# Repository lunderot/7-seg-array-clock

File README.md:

# 7 segment array clock
A clock made of 144 individual 7-segment displays. Uses a ESP8266 and MAX7219.

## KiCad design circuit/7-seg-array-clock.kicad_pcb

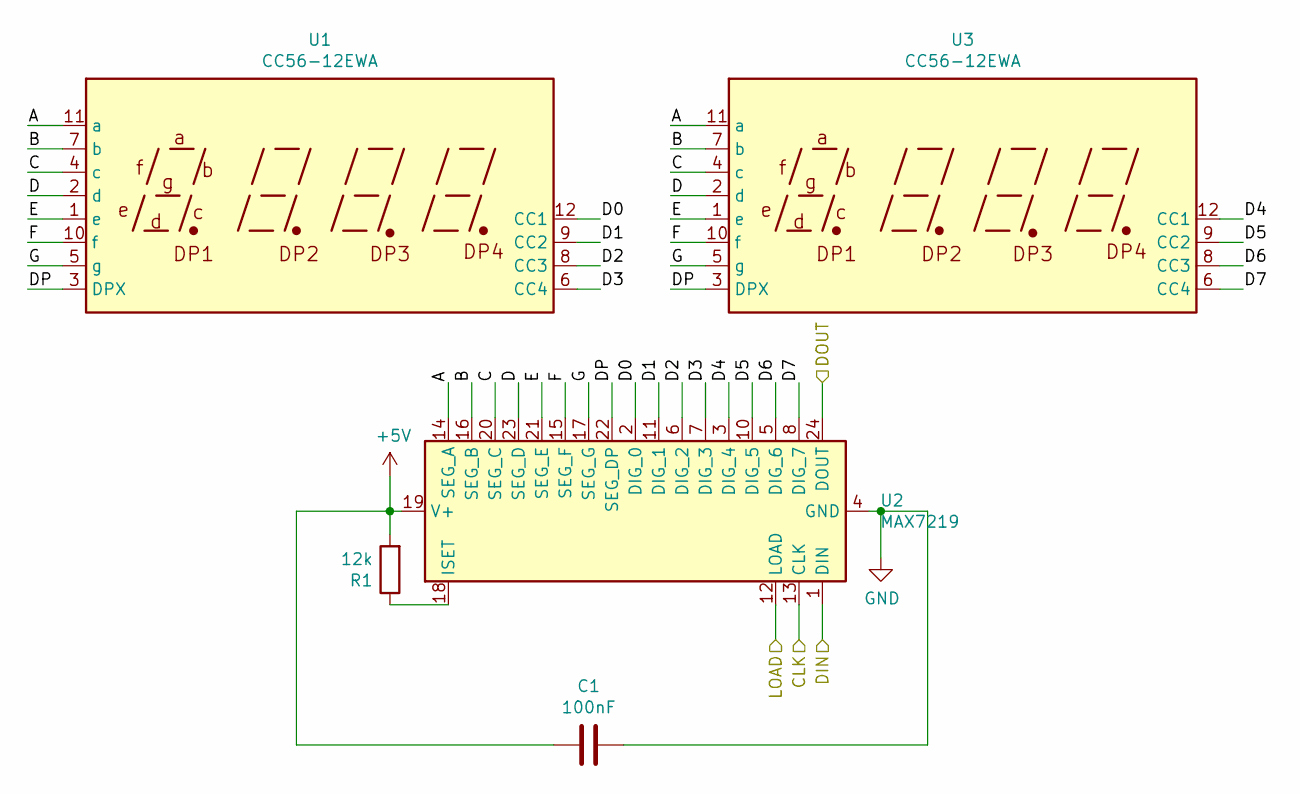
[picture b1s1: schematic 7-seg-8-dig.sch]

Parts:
C1: 100nF; C_0805_2012Metric_Pad1.15x1.40mm_HandSolder
R1: 12k; R_0805_2012Metric_Pad1.15x1.40mm_HandSolder
U1, U3: CC56-12EWA; 7seg
U2: MAX7219; SOIC-24W_7.5x15.4mm_P1.27mm

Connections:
+5V: C1.2, R1.2, U2.19 (V+); also elsewhere on the board
/display0/A: U1.11 (a), U2.14 (SEG_A), U3.11 (a)
/display0/B: U1.7 (b), U2.16 (SEG_B), U3.7 (b)
/display0/C: U1.4 (c), U2.20 (SEG_C), U3.4 (c)
/display0/D: U1.2 (d), U2.23 (SEG_D), U3.2 (d)
/display0/D0: U1.12 (CC1), U2.2 (DIG_0)
/display0/D1: U1.9 (CC2), U2.11 (DIG_1)
/display0/D2: U1.8 (CC3), U2.6 (DIG_2)
/display0/D3: U1.6 (CC4), U2.7 (DIG_3)
/display0/D4: U2.3 (DIG_4), U3.12 (CC1)
/display0/D5: U2.10 (DIG_5), U3.9 (CC2)
/display0/D6: U2.5 (DIG_6), U3.8 (CC3)
/display0/D7: U2.8 (DIG_7), U3.6 (CC4)
/display0/DIN: U2.1 (DIN); also elsewhere on the board
/display0/DP: U1.3 (DPX), U2.22 (SEG_DP), U3.3 (DPX)
/display0/E: U1.1 (e), U2.21 (SEG_E), U3.1 (e)
/display0/F: U1.10 (f), U2.15 (SEG_F), U3.10 (f)
/display0/G: U1.5 (g), U2.17 (SEG_G), U3.5 (g)
/display1/DIN: U2.24 (DOUT); also elsewhere on the board
CLK: U2.13 (CLK); also elsewhere on the board
GND: C1.1, U2.4 (GND), U2.9 (GND); also elsewhere on the board
LOAD: U2.12 (LOAD); also elsewhere on the board
unnamed: R1.1, U2.18 (ISET)

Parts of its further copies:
C2, C3, C4, C5, C6, C7, C8, C9, C10, C11, C12, C13, C14, C15, C16, C17, C18: 100nF; C_0805_2012Metric_Pad1.15x1.40mm_HandSolder
R2, R3, R4, R5, R6, R7, R8, R9, R10, R11, R12, R13, R14, R15, R16, R17, R18: 12k; R_0805_2012Metric_Pad1.15x1.40mm_HandSolder
U4, U6, U8, U10, U11, U13, U14, U16, U17, U19, U20, U22, U23, U25, U26, U28, U29, U31, U32, U34, U35, U37, U38, U40, U41, U43, U44, U46, U47, U49, U50, U52, U53, U55: CC56-12EWA; 7seg
U5, U9, U12, U15, U18, U21, U24, U27, U30, U33, U36, U39, U42, U45, U48, U51, U54: MAX7219; SOIC-24W_7.5x15.4mm_P1.27mm

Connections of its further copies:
+5V: C2.2, C3.2, C4.2, C5.2, C6.2, C7.2, C8.2, C9.2, C10.2, C11.2, C12.2, C13.2, C14.2, C15.2, C16.2, C17.2, C18.2, R2.2, R3.2, R4.2, R5.2, R6.2, R7.2, R8.2, R9.2, R10.2, R11.2, R12.2, R13.2, R14.2, R15.2, R16.2, R17.2, R18.2, U5.19 (V+), U9.19 (V+), U12.19 (V+), U15.19 (V+), U18.19 (V+), U21.19 (V+), U24.19 (V+), U27.19 (V+), U30.19 (V+), U33.19 (V+), U36.19 (V+), U39.19 (V+), U42.19 (V+), U45.19 (V+), U48.19 (V+), U51.19 (V+), U54.19 (V+); also elsewhere on the board
/display1/A: U4.11 (a), U5.14 (SEG_A), U6.11 (a)
/display1/B: U4.7 (b), U5.16 (SEG_B), U6.7 (b)
/display1/C: U4.4 (c), U5.20 (SEG_C), U6.4 (c)
/display1/D: U4.2 (d), U5.23 (SEG_D), U6.2 (d)
/display1/D0: U4.12 (CC1), U5.2 (DIG_0)
/display1/D1: U4.9 (CC2), U5.11 (DIG_1)
/display1/D2: U4.8 (CC3), U5.6 (DIG_2)
/display1/D3: U4.6 (CC4), U5.7 (DIG_3)
/display1/D4: U5.3 (DIG_4), U6.12 (CC1)
/display1/D5: U5.10 (DIG_5), U6.9 (CC2)
/display1/D6: U5.5 (DIG_6), U6.8 (CC3)
/display1/D7: U5.8 (DIG_7), U6.6 (CC4)
/display1/DIN: U5.1 (DIN); also elsewhere on the board
/display1/DP: U4.3 (DPX), U5.22 (SEG_DP), U6.3 (DPX)
/display1/E: U4.1 (e), U5.21 (SEG_E), U6.1 (e)
/display1/F: U4.10 (f), U5.15 (SEG_F), U6.10 (f)
/display1/G: U4.5 (g), U5.17 (SEG_G), U6.5 (g)
/display3/A: U8.11 (a), U9.14 (SEG_A), U10.11 (a)
/display3/B: U8.7 (b), U9.16 (SEG_B), U10.7 (b)
/display3/C: U8.4 (c), U9.20 (SEG_C), U10.4 (c)
/display3/D: U8.2 (d), U9.23 (SEG_D), U10.2 (d)
/display3/D0: U8.12 (CC1), U9.2 (DIG_0)
/display3/D1: U8.9 (CC2), U9.11 (DIG_1)
/display3/D2: U8.8 (CC3), U9.6 (DIG_2)
/display3/D3: U8.6 (CC4), U9.7 (DIG_3)
/display3/D4: U9.3 (DIG_4), U10.12 (CC1)
/display3/D5: U9.10 (DIG_5), U10.9 (CC2)
/display3/D6: U9.5 (DIG_6), U10.8 (CC3)
/display3/D7: U9.8 (DIG_7), U10.6 (CC4)
/display3/DIN: U5.24 (DOUT), U9.1 (DIN)
/display3/DP: U8.3 (DPX), U9.22 (SEG_DP), U10.3 (DPX)
/display3/E: U8.1 (e), U9.21 (SEG_E), U10.1 (e)
/display3/F: U8.10 (f), U9.15 (SEG_F), U10.10 (f)
/display3/G: U8.5 (g), U9.17 (SEG_G), U10.5 (g)
/display4/A: U11.11 (a), U12.14 (SEG_A), U13.11 (a)
/display4/B: U11.7 (b), U12.16 (SEG_B), U13.7 (b)
/display4/C: U11.4 (c), U12.20 (SEG_C), U13.4 (c)
/display4/D: U11.2 (d), U12.23 (SEG_D), U13.2 (d)
/display4/D0: U11.12 (CC1), U12.2 (DIG_0)
/display4/D1: U11.9 (CC2), U12.11 (DIG_1)
/display4/D2: U11.8 (CC3), U12.6 (DIG_2)
/display4/D3: U11.6 (CC4), U12.7 (DIG_3)
/display4/D4: U12.3 (DIG_4), U13.12 (CC1)
/display4/D5: U12.10 (DIG_5), U13.9 (CC2)
/display4/D6: U12.5 (DIG_6), U13.8 (CC3)
/display4/D7: U12.8 (DIG_7), U13.6 (CC4)
/display4/DIN: U9.24 (DOUT), U12.1 (DIN)
/display4/DP: U11.3 (DPX), U12.22 (SEG_DP), U13.3 (DPX)
/display4/E: U11.1 (e), U12.21 (SEG_E), U13.1 (e)
/display4/F: U11.10 (f), U12.15 (SEG_F), U13.10 (f)
/display4/G: U11.5 (g), U12.17 (SEG_G), U13.5 (g)
/display5/A: U14.11 (a), U15.14 (SEG_A), U16.11 (a)
/display5/B: U14.7 (b), U15.16 (SEG_B), U16.7 (b)
/display5/C: U14.4 (c), U15.20 (SEG_C), U16.4 (c)
/display5/D: U14.2 (d), U15.23 (SEG_D), U16.2 (d)
/display5/D0: U14.12 (CC1), U15.2 (DIG_0)
/display5/D1: U14.9 (CC2), U15.11 (DIG_1)
/display5/D2: U14.8 (CC3), U15.6 (DIG_2)
/display5/D3: U14.6 (CC4), U15.7 (DIG_3)
/display5/D4: U15.3 (DIG_4), U16.12 (CC1)
/display5/D5: U15.10 (DIG_5), U16.9 (CC2)
/display5/D6: U15.5 (DIG_6), U16.8 (CC3)
/display5/D7: U15.8 (DIG_7), U16.6 (CC4)
/display5/DIN: U12.24 (DOUT), U15.1 (DIN)
/display5/DP: U14.3 (DPX), U15.22 (SEG_DP), U16.3 (DPX)
/display5/E: U14.1 (e), U15.21 (SEG_E), U16.1 (e)
/display5/F: U14.10 (f), U15.15 (SEG_F), U16.10 (f)
/display5/G: U14.5 (g), U15.17 (SEG_G), U16.5 (g)
/display6/A: U17.11 (a), U18.14 (SEG_A), U19.11 (a)
/display6/B: U17.7 (b), U18.16 (SEG_B), U19.7 (b)
/display6/C: U17.4 (c), U18.20 (SEG_C), U19.4 (c)
/display6/D: U17.2 (d), U18.23 (SEG_D), U19.2 (d)
/display6/D0: U17.12 (CC1), U18.2 (DIG_0)
/display6/D1: U17.9 (CC2), U18.11 (DIG_1)
/display6/D2: U17.8 (CC3), U18.6 (DIG_2)
/display6/D3: U17.6 (CC4), U18.7 (DIG_3)
/display6/D4: U18.3 (DIG_4), U19.12 (CC1)
/display6/D5: U18.10 (DIG_5), U19.9 (CC2)
/display6/D6: U18.5 (DIG_6), U19.8 (CC3)
/display6/D7: U18.8 (DIG_7), U19.6 (CC4)
/display6/DIN: U15.24 (DOUT), U18.1 (DIN)
/display6/DP: U17.3 (DPX), U18.22 (SEG_DP), U19.3 (DPX)
/display6/E: U17.1 (e), U18.21 (SEG_E), U19.1 (e)
/display6/F: U17.10 (f), U18.15 (SEG_F), U19.10 (f)
/display6/G: U17.5 (g), U18.17 (SEG_G), U19.5 (g)
/display7/A: U20.11 (a), U21.14 (SEG_A), U22.11 (a)
/display7/B: U20.7 (b), U21.16 (SEG_B), U22.7 (b)
/display7/C: U20.4 (c), U21.20 (SEG_C), U22.4 (c)
/display7/D: U20.2 (d), U21.23 (SEG_D), U22.2 (d)
/display7/D0: U20.12 (CC1), U21.2 (DIG_0)
/display7/D1: U20.9 (CC2), U21.11 (DIG_1)
/display7/D2: U20.8 (CC3), U21.6 (DIG_2)
/display7/D3: U20.6 (CC4), U21.7 (DIG_3)
/display7/D4: U21.3 (DIG_4), U22.12 (CC1)
/display7/D5: U21.10 (DIG_5), U22.9 (CC2)
/display7/D6: U21.5 (DIG_6), U22.8 (CC3)
/display7/D7: U21.8 (DIG_7), U22.6 (CC4)
/display7/DIN: U18.24 (DOUT), U21.1 (DIN)
/display7/DP: U20.3 (DPX), U21.22 (SEG_DP), U22.3 (DPX)
/display7/E: U20.1 (e), U21.21 (SEG_E), U22.1 (e)
/display7/F: U20.10 (f), U21.15 (SEG_F), U22.10 (f)
/display7/G: U20.5 (g), U21.17 (SEG_G), U22.5 (g)
/display8/A: U23.11 (a), U24.14 (SEG_A), U25.11 (a)
/display8/B: U23.7 (b), U24.16 (SEG_B), U25.7 (b)
/display8/C: U23.4 (c), U24.20 (SEG_C), U25.4 (c)
/display8/D: U23.2 (d), U24.23 (SEG_D), U25.2 (d)
/display8/D0: U23.12 (CC1), U24.2 (DIG_0)
/display8/D1: U23.9 (CC2), U24.11 (DIG_1)
/display8/D2: U23.8 (CC3), U24.6 (DIG_2)
/display8/D3: U23.6 (CC4), U24.7 (DIG_3)
/display8/D4: U24.3 (DIG_4), U25.12 (CC1)
/display8/D5: U24.10 (DIG_5), U25.9 (CC2)
/display8/D6: U24.5 (DIG_6), U25.8 (CC3)
/display8/D7: U24.8 (DIG_7), U25.6 (CC4)
/display8/DIN: U21.24 (DOUT), U24.1 (DIN)
/display8/DP: U23.3 (DPX), U24.22 (SEG_DP), U25.3 (DPX)
/display8/E: U23.1 (e), U24.21 (SEG_E), U25.1 (e)
/display8/F: U23.10 (f), U24.15 (SEG_F), U25.10 (f)
/display8/G: U23.5 (g), U24.17 (SEG_G), U25.5 (g)
/display9/A: U26.11 (a), U27.14 (SEG_A), U28.11 (a)
/display9/B: U26.7 (b), U27.16 (SEG_B), U28.7 (b)
/display9/C: U26.4 (c), U27.20 (SEG_C), U28.4 (c)
/display9/D: U26.2 (d), U27.23 (SEG_D), U28.2 (d)
/display9/D0: U26.12 (CC1), U27.2 (DIG_0)
/display9/D1: U26.9 (CC2), U27.11 (DIG_1)
/display9/D2: U26.8 (CC3), U27.6 (DIG_2)
/display9/D3: U26.6 (CC4), U27.7 (DIG_3)
/display9/D4: U27.3 (DIG_4), U28.12 (CC1)
/display9/D5: U27.10 (DIG_5), U28.9 (CC2)
/display9/D6: U27.5 (DIG_6), U28.8 (CC3)
/display9/D7: U27.8 (DIG_7), U28.6 (CC4)
/display9/DIN: U24.24 (DOUT), U27.1 (DIN)
/display9/DP: U26.3 (DPX), U27.22 (SEG_DP), U28.3 (DPX)
/display9/E: U26.1 (e), U27.21 (SEG_E), U28.1 (e)
/display9/F: U26.10 (f), U27.15 (SEG_F), U28.10 (f)
/display9/G: U26.5 (g), U27.17 (SEG_G), U28.5 (g)
/display10/A: U29.11 (a), U30.14 (SEG_A), U31.11 (a)
/display10/B: U29.7 (b), U30.16 (SEG_B), U31.7 (b)
/display10/C: U29.4 (c), U30.20 (SEG_C), U31.4 (c)
/display10/D: U29.2 (d), U30.23 (SEG_D), U31.2 (d)
/display10/D0: U29.12 (CC1), U30.2 (DIG_0)
/display10/D1: U29.9 (CC2), U30.11 (DIG_1)
/display10/D2: U29.8 (CC3), U30.6 (DIG_2)
/display10/D3: U29.6 (CC4), U30.7 (DIG_3)
/display10/D4: U30.3 (DIG_4), U31.12 (CC1)
/display10/D5: U30.10 (DIG_5), U31.9 (CC2)
/display10/D6: U30.5 (DIG_6), U31.8 (CC3)
/display10/D7: U30.8 (DIG_7), U31.6 (CC4)
/display10/DIN: U27.24 (DOUT), U30.1 (DIN)
/display10/DP: U29.3 (DPX), U30.22 (SEG_DP), U31.3 (DPX)
/display10/E: U29.1 (e), U30.21 (SEG_E), U31.1 (e)
/display10/F: U29.10 (f), U30.15 (SEG_F), U31.10 (f)
/display10/G: U29.5 (g), U30.17 (SEG_G), U31.5 (g)
/display11/A: U32.11 (a), U33.14 (SEG_A), U34.11 (a)
/display11/B: U32.7 (b), U33.16 (SEG_B), U34.7 (b)
/display11/C: U32.4 (c), U33.20 (SEG_C), U34.4 (c)
/display11/D: U32.2 (d), U33.23 (SEG_D), U34.2 (d)
/display11/D0: U32.12 (CC1), U33.2 (DIG_0)
/display11/D1: U32.9 (CC2), U33.11 (DIG_1)
/display11/D2: U32.8 (CC3), U33.6 (DIG_2)
/display11/D3: U32.6 (CC4), U33.7 (DIG_3)
/display11/D4: U33.3 (DIG_4), U34.12 (CC1)
/display11/D5: U33.10 (DIG_5), U34.9 (CC2)
/display11/D6: U33.5 (DIG_6), U34.8 (CC3)
/display11/D7: U33.8 (DIG_7), U34.6 (CC4)
/display11/DIN: U30.24 (DOUT), U33.1 (DIN)
/display11/DP: U32.3 (DPX), U33.22 (SEG_DP), U34.3 (DPX)
/display11/E: U32.1 (e), U33.21 (SEG_E), U34.1 (e)
/display11/F: U32.10 (f), U33.15 (SEG_F), U34.10 (f)
/display11/G: U32.5 (g), U33.17 (SEG_G), U34.5 (g)
/display12/A: U35.11 (a), U36.14 (SEG_A), U37.11 (a)
/display12/B: U35.7 (b), U36.16 (SEG_B), U37.7 (b)
/display12/C: U35.4 (c), U36.20 (SEG_C), U37.4 (c)
/display12/D: U35.2 (d), U36.23 (SEG_D), U37.2 (d)
/display12/D0: U35.12 (CC1), U36.2 (DIG_0)
/display12/D1: U35.9 (CC2), U36.11 (DIG_1)
/display12/D2: U35.8 (CC3), U36.6 (DIG_2)
/display12/D3: U35.6 (CC4), U36.7 (DIG_3)
/display12/D4: U36.3 (DIG_4), U37.12 (CC1)
/display12/D5: U36.10 (DIG_5), U37.9 (CC2)
/display12/D6: U36.5 (DIG_6), U37.8 (CC3)
/display12/D7: U36.8 (DIG_7), U37.6 (CC4)
/display12/DIN: U33.24 (DOUT), U36.1 (DIN)
/display12/DP: U35.3 (DPX), U36.22 (SEG_DP), U37.3 (DPX)
/display12/E: U35.1 (e), U36.21 (SEG_E), U37.1 (e)
/display12/F: U35.10 (f), U36.15 (SEG_F), U37.10 (f)
/display12/G: U35.5 (g), U36.17 (SEG_G), U37.5 (g)
/display13/A: U38.11 (a), U39.14 (SEG_A), U40.11 (a)
/display13/B: U38.7 (b), U39.16 (SEG_B), U40.7 (b)
/display13/C: U38.4 (c), U39.20 (SEG_C), U40.4 (c)
/display13/D: U38.2 (d), U39.23 (SEG_D), U40.2 (d)
/display13/D0: U38.12 (CC1), U39.2 (DIG_0)
/display13/D1: U38.9 (CC2), U39.11 (DIG_1)
/display13/D2: U38.8 (CC3), U39.6 (DIG_2)
/display13/D3: U38.6 (CC4), U39.7 (DIG_3)
/display13/D4: U39.3 (DIG_4), U40.12 (CC1)
/display13/D5: U39.10 (DIG_5), U40.9 (CC2)
/display13/D6: U39.5 (DIG_6), U40.8 (CC3)
/display13/D7: U39.8 (DIG_7), U40.6 (CC4)
/display13/DIN: U36.24 (DOUT), U39.1 (DIN)
/display13/DP: U38.3 (DPX), U39.22 (SEG_DP), U40.3 (DPX)
/display13/E: U38.1 (e), U39.21 (SEG_E), U40.1 (e)
/display13/F: U38.10 (f), U39.15 (SEG_F), U40.10 (f)
/display13/G: U38.5 (g), U39.17 (SEG_G), U40.5 (g)
/display14/A: U41.11 (a), U42.14 (SEG_A), U43.11 (a)
/display14/B: U41.7 (b), U42.16 (SEG_B), U43.7 (b)
/display14/C: U41.4 (c), U42.20 (SEG_C), U43.4 (c)
/display14/D: U41.2 (d), U42.23 (SEG_D), U43.2 (d)
/display14/D0: U41.12 (CC1), U42.2 (DIG_0)
/display14/D1: U41.9 (CC2), U42.11 (DIG_1)
/display14/D2: U41.8 (CC3), U42.6 (DIG_2)
/display14/D3: U41.6 (CC4), U42.7 (DIG_3)
/display14/D4: U42.3 (DIG_4), U43.12 (CC1)
/display14/D5: U42.10 (DIG_5), U43.9 (CC2)
/display14/D6: U42.5 (DIG_6), U43.8 (CC3)
/display14/D7: U42.8 (DIG_7), U43.6 (CC4)
/display14/DIN: U39.24 (DOUT), U42.1 (DIN)
/display14/DP: U41.3 (DPX), U42.22 (SEG_DP), U43.3 (DPX)
/display14/E: U41.1 (e), U42.21 (SEG_E), U43.1 (e)
/display14/F: U41.10 (f), U42.15 (SEG_F), U43.10 (f)
/display14/G: U41.5 (g), U42.17 (SEG_G), U43.5 (g)
/display15/A: U44.11 (a), U45.14 (SEG_A), U46.11 (a)
/display15/B: U44.7 (b), U45.16 (SEG_B), U46.7 (b)
/display15/C: U44.4 (c), U45.20 (SEG_C), U46.4 (c)
/display15/D: U44.2 (d), U45.23 (SEG_D), U46.2 (d)
/display15/D0: U44.12 (CC1), U45.2 (DIG_0)
/display15/D1: U44.9 (CC2), U45.11 (DIG_1)
/display15/D2: U44.8 (CC3), U45.6 (DIG_2)
/display15/D3: U44.6 (CC4), U45.7 (DIG_3)
/display15/D4: U45.3 (DIG_4), U46.12 (CC1)
/display15/D5: U45.10 (DIG_5), U46.9 (CC2)
/display15/D6: U45.5 (DIG_6), U46.8 (CC3)
/display15/D7: U45.8 (DIG_7), U46.6 (CC4)
/display15/DIN: U42.24 (DOUT), U45.1 (DIN)
/display15/DP: U44.3 (DPX), U45.22 (SEG_DP), U46.3 (DPX)
/display15/E: U44.1 (e), U45.21 (SEG_E), U46.1 (e)
/display15/F: U44.10 (f), U45.15 (SEG_F), U46.10 (f)
/display15/G: U44.5 (g), U45.17 (SEG_G), U46.5 (g)
/display16/A: U47.11 (a), U48.14 (SEG_A), U49.11 (a)
/display16/B: U47.7 (b), U48.16 (SEG_B), U49.7 (b)
/display16/C: U47.4 (c), U48.20 (SEG_C), U49.4 (c)
/display16/D: U47.2 (d), U48.23 (SEG_D), U49.2 (d)
/display16/D0: U47.12 (CC1), U48.2 (DIG_0)
/display16/D1: U47.9 (CC2), U48.11 (DIG_1)
/display16/D2: U47.8 (CC3), U48.6 (DIG_2)
/display16/D3: U47.6 (CC4), U48.7 (DIG_3)
/display16/D4: U48.3 (DIG_4), U49.12 (CC1)
/display16/D5: U48.10 (DIG_5), U49.9 (CC2)
/display16/D6: U48.5 (DIG_6), U49.8 (CC3)
/display16/D7: U48.8 (DIG_7), U49.6 (CC4)
/display16/DIN: U45.24 (DOUT), U48.1 (DIN)
/display16/DP: U47.3 (DPX), U48.22 (SEG_DP), U49.3 (DPX)
/display16/E: U47.1 (e), U48.21 (SEG_E), U49.1 (e)
/display16/F: U47.10 (f), U48.15 (SEG_F), U49.10 (f)
/display16/G: U47.5 (g), U48.17 (SEG_G), U49.5 (g)
/display17/A: U50.11 (a), U51.14 (SEG_A), U52.11 (a)
/display17/B: U50.7 (b), U51.16 (SEG_B), U52.7 (b)
/display17/C: U50.4 (c), U51.20 (SEG_C), U52.4 (c)
/display17/D: U50.2 (d), U51.23 (SEG_D), U52.2 (d)
/display17/D0: U50.12 (CC1), U51.2 (DIG_0)
/display17/D1: U50.9 (CC2), U51.11 (DIG_1)
/display17/D2: U50.8 (CC3), U51.6 (DIG_2)
/display17/D3: U50.6 (CC4), U51.7 (DIG_3)
/display17/D4: U51.3 (DIG_4), U52.12 (CC1)
/display17/D5: U51.10 (DIG_5), U52.9 (CC2)
/display17/D6: U51.5 (DIG_6), U52.8 (CC3)
/display17/D7: U51.8 (DIG_7), U52.6 (CC4)
/display17/DIN: U48.24 (DOUT), U51.1 (DIN)
/display17/DP: U50.3 (DPX), U51.22 (SEG_DP), U52.3 (DPX)
/display17/E: U50.1 (e), U51.21 (SEG_E), U52.1 (e)
/display17/F: U50.10 (f), U51.15 (SEG_F), U52.10 (f)
/display17/G: U50.5 (g), U51.17 (SEG_G), U52.5 (g)
/display18/A: U53.11 (a), U54.14 (SEG_A), U55.11 (a)
/display18/B: U53.7 (b), U54.16 (SEG_B), U55.7 (b)
/display18/C: U53.4 (c), U54.20 (SEG_C), U55.4 (c)
/display18/D: U53.2 (d), U54.23 (SEG_D), U55.2 (d)
/display18/D0: U53.12 (CC1), U54.2 (DIG_0)
/display18/D1: U53.9 (CC2), U54.11 (DIG_1)
/display18/D2: U53.8 (CC3), U54.6 (DIG_2)
/display18/D3: U53.6 (CC4), U54.7 (DIG_3)
/display18/D4: U54.3 (DIG_4), U55.12 (CC1)
/display18/D5: U54.10 (DIG_5), U55.9 (CC2)
/display18/D6: U54.5 (DIG_6), U55.8 (CC3)
/display18/D7: U54.8 (DIG_7), U55.6 (CC4)
/display18/DIN: U51.24 (DOUT), U54.1 (DIN)
/display18/DOUT: U54.24 (DOUT)
/display18/DP: U53.3 (DPX), U54.22 (SEG_DP), U55.3 (DPX)
/display18/E: U53.1 (e), U54.21 (SEG_E), U55.1 (e)
/display18/F: U53.10 (f), U54.15 (SEG_F), U55.10 (f)
/display18/G: U53.5 (g), U54.17 (SEG_G), U55.5 (g)
CLK: U5.13 (CLK), U9.13 (CLK), U12.13 (CLK), U15.13 (CLK), U18.13 (CLK), U21.13 (CLK), U24.13 (CLK), U27.13 (CLK), U30.13 (CLK), U33.13 (CLK), U36.13 (CLK), U39.13 (CLK), U42.13 (CLK), U45.13 (CLK), U48.13 (CLK), U51.13 (CLK), U54.13 (CLK); also elsewhere on the board
GND: C2.1, C3.1, C4.1, C5.1, C6.1, C7.1, C8.1, C9.1, C10.1, C11.1, C12.1, C13.1, C14.1, C15.1, C16.1, C17.1, C18.1, U5.4 (GND), U5.9 (GND), U9.4 (GND), U9.9 (GND), U12.4 (GND), U12.9 (GND), U15.4 (GND), U15.9 (GND), U18.4 (GND), U18.9 (GND), U21.4 (GND), U21.9 (GND), U24.4 (GND), U24.9 (GND), U27.4 (GND), U27.9 (GND), U30.4 (GND), U30.9 (GND), U33.4 (GND), U33.9 (GND), U36.4 (GND), U36.9 (GND), U39.4 (GND), U39.9 (GND), U42.4 (GND), U42.9 (GND), U45.4 (GND), U45.9 (GND), U48.4 (GND), U48.9 (GND), U51.4 (GND), U51.9 (GND), U54.4 (GND), U54.9 (GND); also elsewhere on the board
LOAD: U5.12 (LOAD), U9.12 (LOAD), U12.12 (LOAD), U15.12 (LOAD), U18.12 (LOAD), U21.12 (LOAD), U24.12 (LOAD), U27.12 (LOAD), U30.12 (LOAD), U33.12 (LOAD), U36.12 (LOAD), U39.12 (LOAD), U42.12 (LOAD), U45.12 (LOAD), U48.12 (LOAD), U51.12 (LOAD), U54.12 (LOAD); also elsewhere on the board
unnamed: R2.1, U5.18 (ISET)
unnamed: R3.1, U9.18 (ISET)
unnamed: R4.1, U12.18 (ISET)
unnamed: R5.1, U15.18 (ISET)
unnamed: R6.1, U18.18 (ISET)
unnamed: R7.1, U21.18 (ISET)
unnamed: R8.1, U24.18 (ISET)
unnamed: R9.1, U27.18 (ISET)
unnamed: R10.1, U30.18 (ISET)
unnamed: R11.1, U33.18 (ISET)
unnamed: R12.1, U36.18 (ISET)
unnamed: R13.1, U39.18 (ISET)
unnamed: R14.1, U42.18 (ISET)
unnamed: R15.1, U45.18 (ISET)
unnamed: R16.1, U48.18 (ISET)
unnamed: R17.1, U51.18 (ISET)
unnamed: R18.1, U54.18 (ISET)

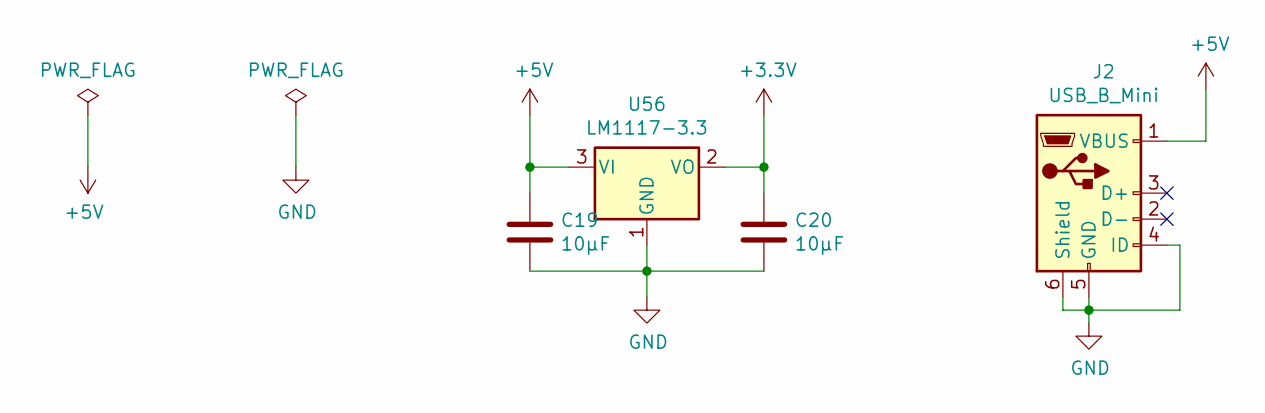
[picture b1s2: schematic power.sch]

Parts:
C19, C20: 10µF; C_0805_2012Metric_Pad1.15x1.40mm_HandSolder
J2: USB_B_Mini; USB_Mini-B_Lumberg_2486_01_Horizontal
U56: LM1117-3.3; SOT-223-3_TabPin2

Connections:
+3V3: C20.1, U56.2 (VO); also elsewhere on the board
+5V: C19.1, J2.1 (VBUS), U56.3 (VI); also elsewhere on the board
GND: C19.2, C20.2, J2.4 (ID), J2.5 (GND), J2.6 (Shield), U56.1 (GND); also elsewhere on the board

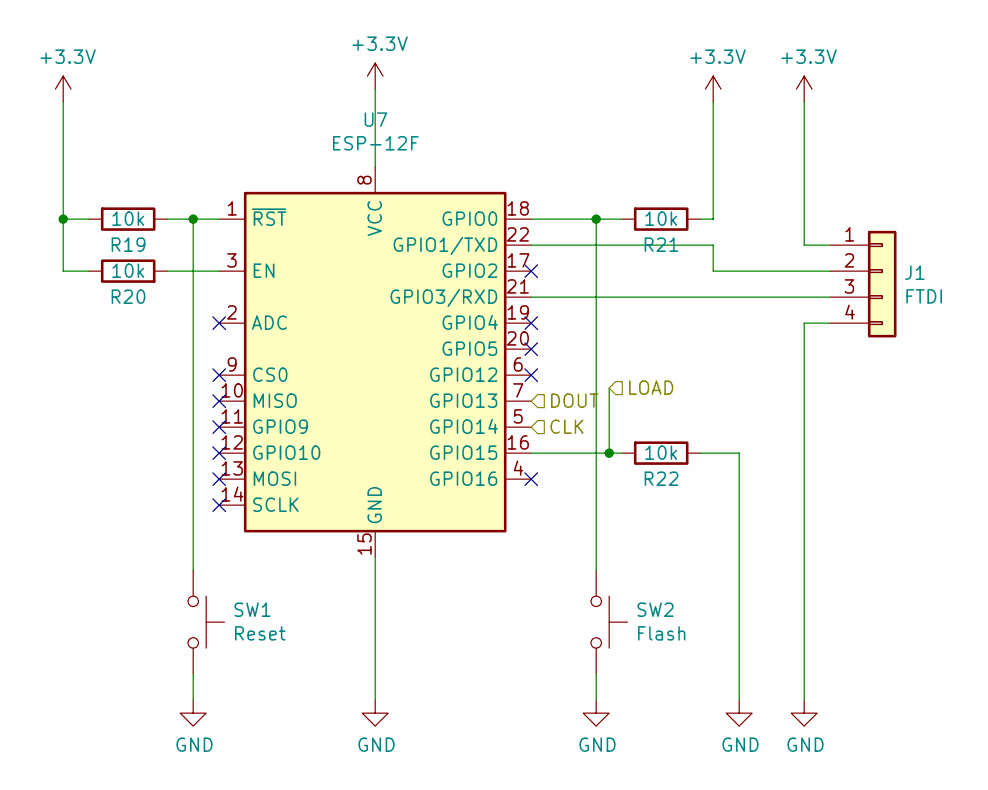
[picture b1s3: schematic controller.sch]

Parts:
J1: FTDI; PinHeader_1x04_P2.54mm_Vertical
R19, R20, R21, R22: 10k; R_0805_2012Metric_Pad1.15x1.40mm_HandSolder
SW1: Reset; SW_SPST_CK_RS282G05A3
SW2: Flash; SW_SPST_CK_RS282G05A3
U7: ESP-12F; ESP-12E

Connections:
+3V3: J1.1, R19.2, R20.1, R21.1, U7.8 (VCC); also elsewhere on the board
/display0/DIN: U7.7 (GPIO13); also elsewhere on the board
CLK: U7.5 (GPIO14); also elsewhere on the board
GND: J1.4, R22.1, SW1.2, SW2.2, U7.15 (GND); also elsewhere on the board
LOAD: R22.2, U7.16 (GPIO15); also elsewhere on the board
unnamed: J1.2, U7.22 (GPIO1/TXD)
unnamed: J1.3, U7.21 (GPIO3/RXD)
unnamed: R19.1, SW1.1, U7.1 (~RST)
unnamed: R20.2, U7.3 (EN)
unnamed: R21.2, SW2.1, U7.18 (GPIO0)

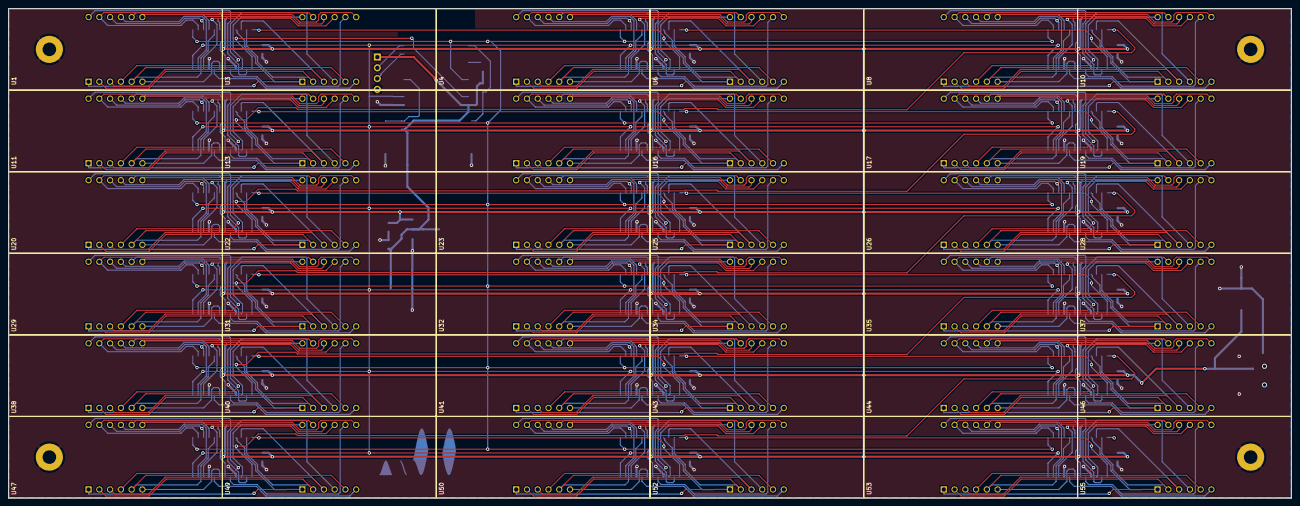
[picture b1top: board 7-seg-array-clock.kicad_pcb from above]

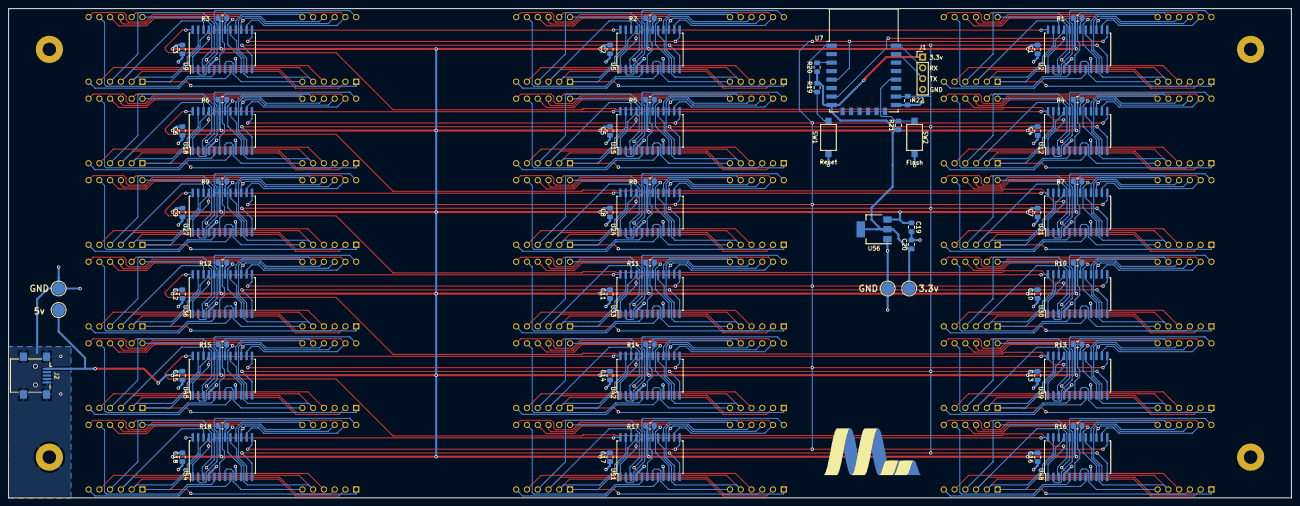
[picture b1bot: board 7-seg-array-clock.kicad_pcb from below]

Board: 2 copper layers, 302.6 x 115.4 mm, 102 parts (66 on the bottom side), 334 nets.

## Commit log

2020-02-01 Completed display circuit and made basic PCB layout
2020-02-01 Added tracks to first display
2020-02-02 Routed all displays
2020-02-02 Updated display footprint
2020-02-02 Added PCB screenshots
2020-02-02 Fixed display clearance issues
2020-02-02 Updated footprint to the proper one
2020-02-05 Added microcontroller circuit
2020-02-09 Added controller to PCB
2020-02-09 Finished PCB
2020-02-23 Added mouting holes
2020-02-23 Changed to use hardware spi
2020-02-23 Added usb power connector
2020-03-08 Added basic code
2020-03-21 Updated 7 segment footprint
2020-03-21 Moved components
2020-03-26 Routed first 8 digits
2020-03-26 Copied tracks to other displays
2020-03-29 Finished board with proper spacing
2020-03-29 Updated 3d model to red segments
2020-04-03 Added logo to PCB
2020-04-03 Added voltage test pads
2020-04-03 Updated PCB pictures
2020-04-18 NTP connection
2020-05-14 Added display test
2020-05-15 Added proper display code
2020-05-15 Added big numbers
2020-05-17 Cleanup
2020-05-17 Added clock function with blinking
2020-05-29 Added test animation
2020-05-29 NTPClient is now a library dependency
2020-07-18 Added CAD files
2020-09-10 Added flat side to spacer
2020-09-19 Activated clock function
2020-09-19 Added readme
2022-01-24 Removed useless config
2022-01-29 Wifi config now stored in eeprom
2022-08-18 Modified 3D-printed part to accept M2 nut
2022-08-18 Wifi config improved
2023-05-23 Added time zone correction
2023-06-02 Fixed time zone correction
2023-06-02 Updated gitignore and project file
